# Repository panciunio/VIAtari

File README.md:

# VIAtari

**Welcome to the VIAtari wiki!**

**Introduction**
Inspiration for this mode I found on Daryl's Computer Hobby Page. Daryl made Composite Video Text/Graphics Display based on ATMEGA8 and drive by VIA6522. This article will show how to build, assembly and connect VIA 6522 IC to Atari and use 2 additional 8-bit parallel ports and serial interface. This is my own project build from scratch but it's nothing modern - this IC was used in C64 to communicate with disk drive. It will be used as additional PIA for manage other equipment.

Notice:
This implementation is designed for Atari 65/130XE with CART/ECI ports available. It's called VIAtariXE

**Why?**
Well, on the market you may find a few sellers which have VIA6522, but...
- this IC is discontinued, don't wait so much time, buy it!
- it's still very useful and may be good alternative for PIA 6520(6521).
- topology and registers covering PIA 6520, so you may use it as equivalent for it. (some pins should be swapped)
- very cheap IC (~2$/piece).

**Best sources**
Original source:
https://systemembedded.eu/viewtopic.php?f=28&t=41

**Discussion (Polish)**

http://www.atari.org.pl/forum/viewtopic.php?id=16098

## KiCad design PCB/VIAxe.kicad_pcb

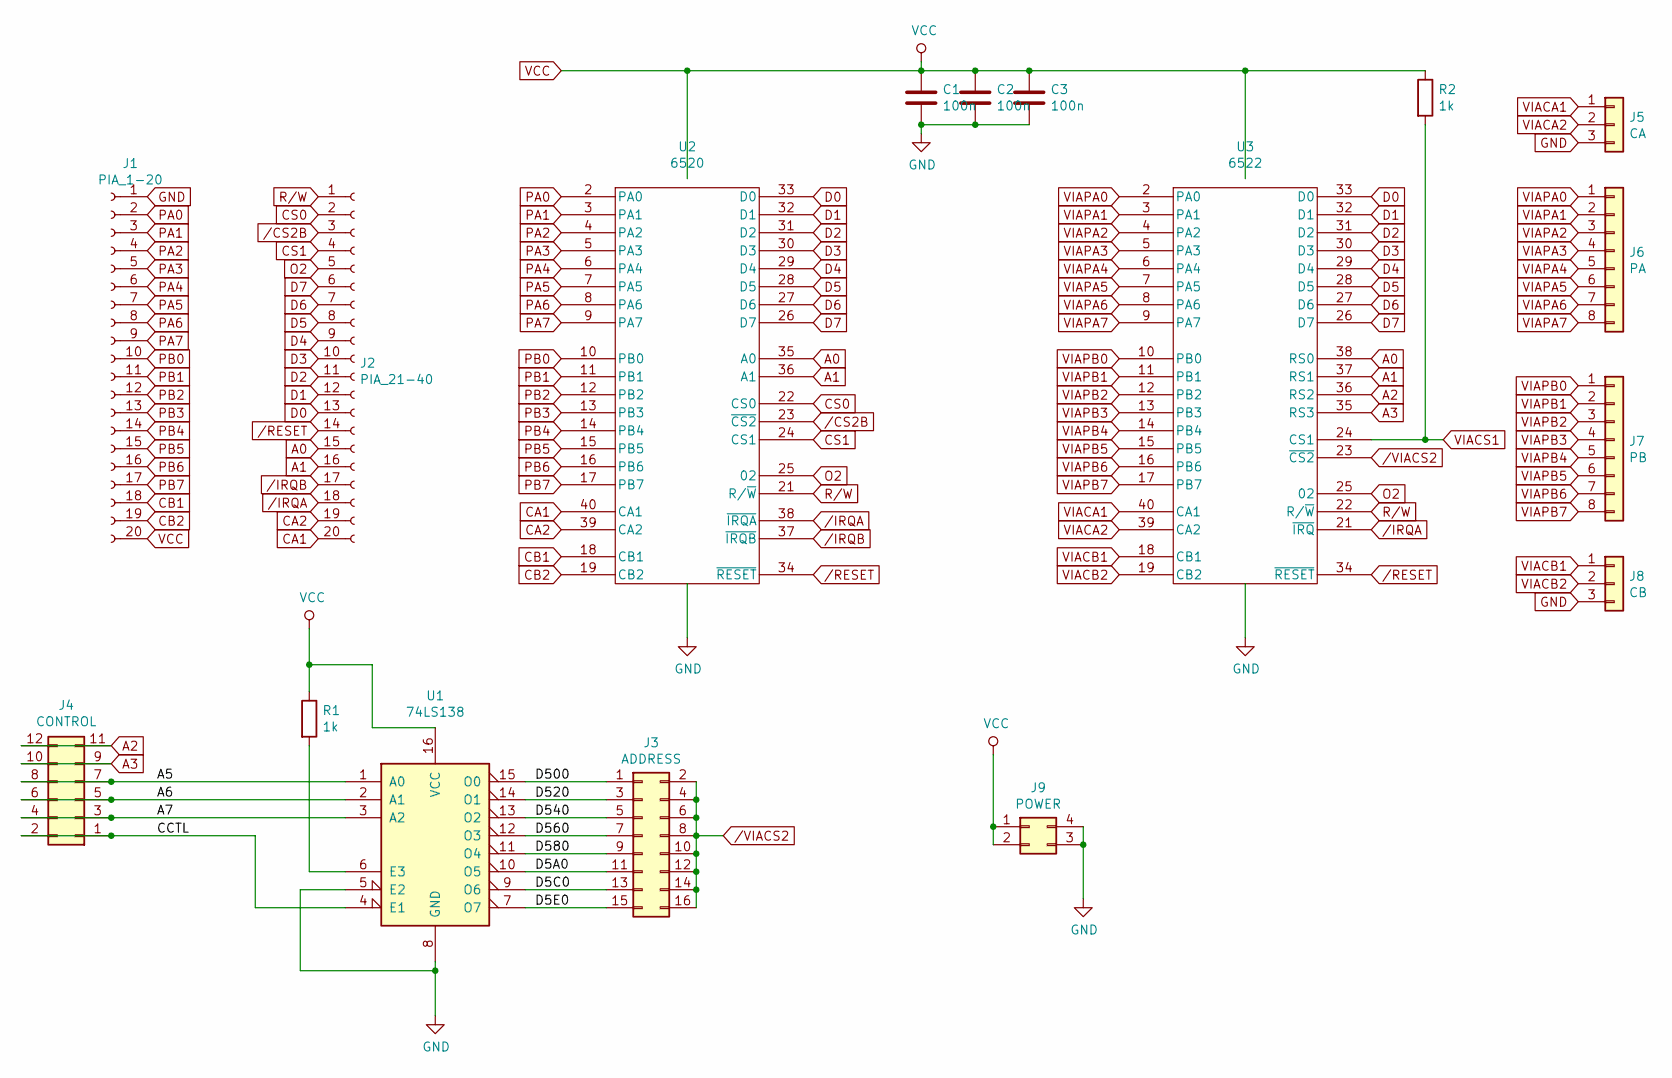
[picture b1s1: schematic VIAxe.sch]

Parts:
C1, C2, C3: 100n; C_1206_3216Metric
J1: PIA_1-20; PinSocket_1x20_P2.54mm_Vertical
J2: PIA_21-40; PinSocket_1x20_P2.54mm_Vertical
J3: ADDRESS; PinHeader_2x08_P2.54mm_Vertical
J4: CONTROL; PinHeader_2x06_P2.54mm_Vertical
J5: CA; PinHeader_1x03_P2.54mm_Vertical
J6: PA; PinHeader_1x08_P2.54mm_Vertical
J7: PB; PinHeader_1x08_P2.54mm_Vertical
J8: CB; PinHeader_1x03_P2.54mm_Vertical
J9: POWER; PinHeader_2x02_P2.54mm_Vertical
R1, R2: 1k; R_1206_3216Metric
U1: 74LS138; SOP-16_4.4x10.4mm_P1.27mm
U2: 6520; DIP-40_W15.24mm_LongPads
U3: 6522; DIP-40_W15.24mm_LongPads

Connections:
/A5: J4.7, J4.8, U1.1 (A0)
/A6: J4.5, J4.6, U1.2 (A1)
/A7: J4.3, J4.4, U1.3 (A2)
/CCTL: J4.1, J4.2, U1.4 (E1)
/CS2B: J2.3, U2.23 (~CS2)
/D5A0: J3.11, U1.10 (O5)
/D5C0: J3.13, U1.9 (O6)
/D5E0: J3.15, U1.7 (O7)
/D500: J3.1, U1.15 (O0)
/D520: J3.3, U1.14 (O1)
/D540: J3.5, U1.13 (O2)
/D560: J3.7, U1.12 (O3)
/D580: J3.9, U1.11 (O4)
/IRQA: J2.18, U2.38 (~IRQA), U3.21 (~IRQ)
/IRQB: J2.17, U2.37 (~IRQB)
/RESET: J2.14, U2.34 (~RESET), U3.34 (~RESET)
/VIACS2: J3.2, J3.4, J3.6, J3.8, J3.10, J3.12, J3.14, J3.16, U3.23 (~CS2)
A0: J2.15, U2.35 (A0), U3.38 (RS0)
A1: J2.16, U2.36 (A1), U3.37 (RS1)
A2: J4.11, J4.12, U3.36 (RS2)
A3: J4.9, J4.10, U3.35 (RS3)
CA1: J2.20, U2.40 (CA1)
CA2: J2.19, U2.39 (CA2)
CB1: J1.18, U2.18 (CB1)
CB2: J1.19, U2.19 (CB2)
CS0: J2.2, U2.22 (CS0)
CS1: J2.4, U2.24 (CS1)
D0: J2.13, U2.33 (D0), U3.33 (D0)
D1: J2.12, U2.32 (D1), U3.32 (D1)
D2: J2.11, U2.31 (D2), U3.31 (D2)
D3: J2.10, U2.30 (D3), U3.30 (D3)
D4: J2.9, U2.29 (D4), U3.29 (D4)
D5: J2.8, U2.28 (D5), U3.28 (D5)
D6: J2.7, U2.27 (D6), U3.27 (D6)
D7: J2.6, U2.26 (D7), U3.26 (D7)
GND: C1.2, C2.2, C3.2, J1.1, J5.3, J8.3, J9.3, J9.4, U1.5 (E2), U1.8 (GND), U2.1 (GND), U3.1 (GND)
unnamed: R1.2, U1.6 (E3)
O2: J2.5, U2.25 (02), U3.25 (02)
PA0: J1.2, U2.2 (PA0)
PA1: J1.3, U2.3 (PA1)
PA2: J1.4, U2.4 (PA2)
PA3: J1.5, U2.5 (PA3)
PA4: J1.6, U2.6 (PA4)
PA5: J1.7, U2.7 (PA5)
PA6: J1.8, U2.8 (PA6)
PA7: J1.9, U2.9 (PA7)
PB0: J1.10, U2.10 (PB0)
PB1: J1.11, U2.11 (PB1)
PB2: J1.12, U2.12 (PB2)
PB3: J1.13, U2.13 (PB3)
PB4: J1.14, U2.14 (PB4)
PB5: J1.15, U2.15 (PB5)
PB6: J1.16, U2.16 (PB6)
PB7: J1.17, U2.17 (PB7)
R/W: J2.1, U2.21 (R/~W), U3.22 (R/~W)
VCC: C1.1, C2.1, C3.1, J1.20, J9.1, J9.2, R1.1, R2.1, U1.16 (VCC), U2.20 (Vcc), U3.20 (Vcc)
VIACA1: J5.1, U3.40 (CA1)
VIACA2: J5.2, U3.39 (CA2)
VIACB1: J8.1, U3.18 (CB1)
VIACB2: J8.2, U3.19 (CB2)
VIACS1: R2.2, U3.24 (CS1)
VIAPA0: J6.1, U3.2 (PA0)
VIAPA1: J6.2, U3.3 (PA1)
VIAPA2: J6.3, U3.4 (PA2)
VIAPA3: J6.4, U3.5 (PA3)
VIAPA4: J6.5, U3.6 (PA4)
VIAPA5: J6.6, U3.7 (PA5)
VIAPA6: J6.7, U3.8 (PA6)
VIAPA7: J6.8, U3.9 (PA7)
VIAPB0: J7.1, U3.10 (PB0)
VIAPB1: J7.2, U3.11 (PB1)
VIAPB2: J7.3, U3.12 (PB2)
VIAPB3: J7.4, U3.13 (PB3)
VIAPB4: J7.5, U3.14 (PB4)
VIAPB5: J7.6, U3.15 (PB5)
VIAPB6: J7.7, U3.16 (PB6)
VIAPB7: J7.8, U3.17 (PB7)

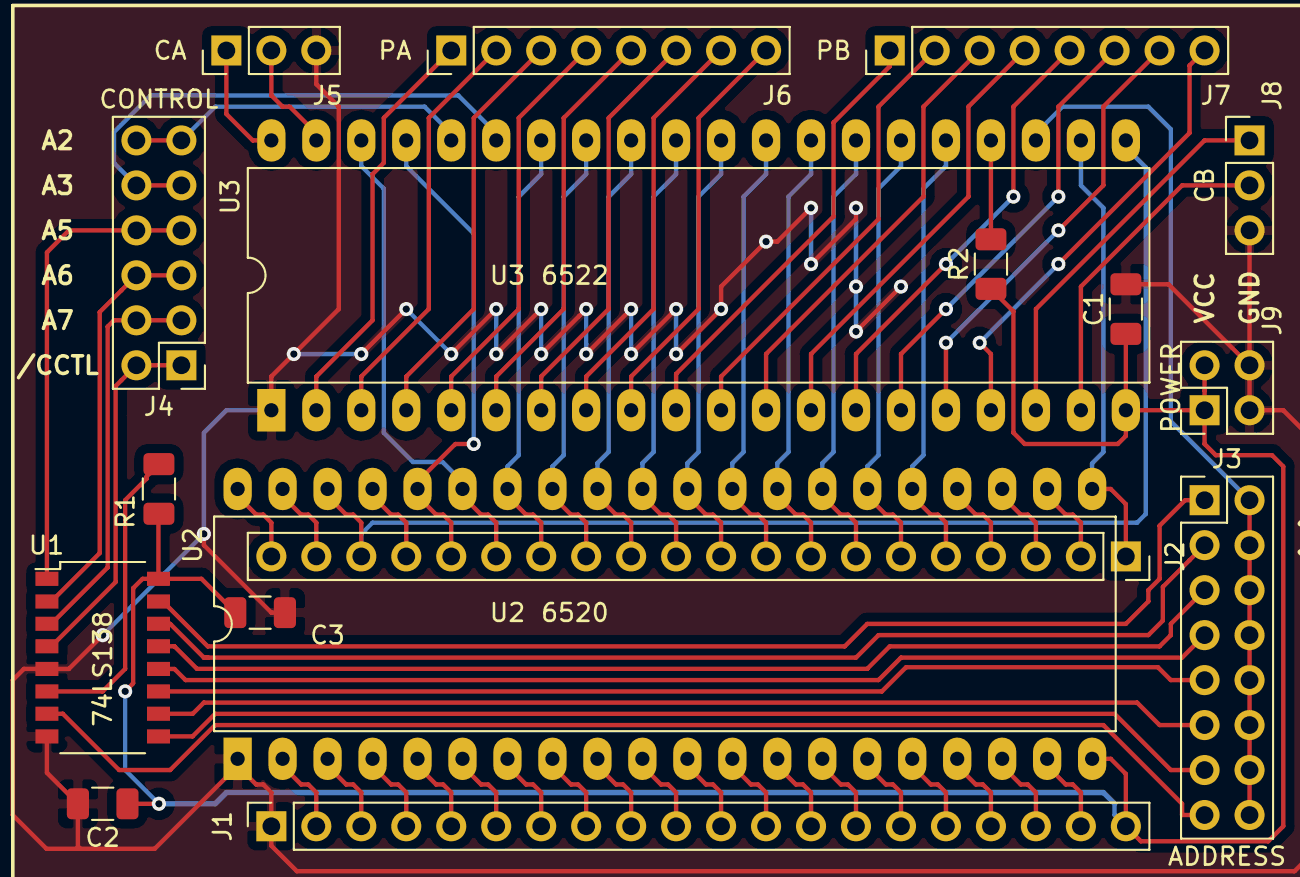
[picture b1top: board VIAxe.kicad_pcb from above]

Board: 2 copper layers, 17 parts (0 on the bottom side), 77 nets.

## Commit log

2019-08-05 new file: PCF8584.inc new file: S1D15705.asm new file: S1D15705.inc new file: VIA6522.asm new file: VIA6522.inc new file: main.asm new file: pcf8584lib.asm
2019-08-05 new file: PCB/VIAtariXE10.zip new file: PCB/VIAxe-B.Cu.gbr new file: PCB/VIAxe-B.Mask.gbr new file: PCB/VIAxe-B.Paste.gbr new file: PCB/VIAxe-B.SilkS.gbr new file: PCB/VIAxe-Edge.Cuts.gbr new file: P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
2019-08-08 v1.0.1 20190808
2019-08-08 v1.0.2 20190908
2019-08-08 v1.0.3 20190808
2019-08-08 v1.0.4 20190808 deleted PCF8584.inc
2019-08-08 v1.0.5 20190808
2019-08-08 v1.0.6 20190808
2019-08-08 v1.0.1 20190807
2019-08-08 Update README.md
    Added discussion chapter
2019-08-09 v1.0.7 20190809
2019-08-22 20190822 v1.0.10
2019-09-26 v1.0.10

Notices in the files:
PCB/VIAxe.kicad_pcb:
VIAtariXE v.1.0 (c) 2019 pancio@pancio.net
